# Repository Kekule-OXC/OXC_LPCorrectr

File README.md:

# OXC_LPCorrectr
LPC rebuild baord for the OG XBOX 1.6 motherboard 

-------------------------------------------------------
This documentation describes Open Hardware and is licensed under the CERN OHL v.1.2.

You may redistribute and modify this documentation under the terms of the CERN OHL v.1.2.(http://ohwr.org/cernohl). 
This documentation is distributed WITHOUT ANY EXPRESS OR IMPLIED WARRANTY, INCLUDING OF MERCHANTABILITY, SATISFACTORY QUALITY AND FITNESS FOR A PARTICULAR PURPOSE. 
Please see the CERN OHL v.1.2 for applicable conditions

-------------------------------------------------------

OXC_LPCorrectr   - README.TXT

Files Included in OXC_LPCorrectr.zip (all files must be included when redistributed):

README.TXT
-This file.
	
CHANGES.TXT
-Describes changes made by the original author or anyone else who alters these files.

OXCLPC_V4_gerbers.zip  
-manufactring files for the LPC correctr board v4
- added LFrame wire to ease OpenXenium install, changed d0 jumper pad

OXCLPC_gerbers.zip
-manufacturing files for the LPC correctr board v3

LPC_install.pdf
-install diagram for v3

LPC v4 install.pdf
-install diagram for v4

cern_ohl_v_1_2.pdf
-CERN OHL v.1.2 License.
	
cern_ohl_v_1_2_howto.pdf
-How to use and comply with the CERN OHL v.1.2 License.
	
-------------------------------------------------------

FABRICATION NOTES

PCB
-The PCB is a 0.8mm thick two layer board, with castellated holes on all sides.

-------------------------------------------------------

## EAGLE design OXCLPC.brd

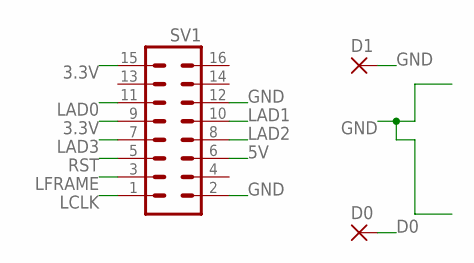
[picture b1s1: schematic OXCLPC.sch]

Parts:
D0, D1: SMD2; SMD1,27-2,54
SV1: MA08-2

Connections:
3.3V: SV1.9, SV1.15
5V: SV1.6
D0: D0.1
GND: D1.1, SV1.2, SV1.12
LAD0: SV1.11
LAD1: SV1.10
LAD2: SV1.8
LAD3: SV1.7
LCLK: SV1.1
LFRAME: SV1.3
RST: SV1.5

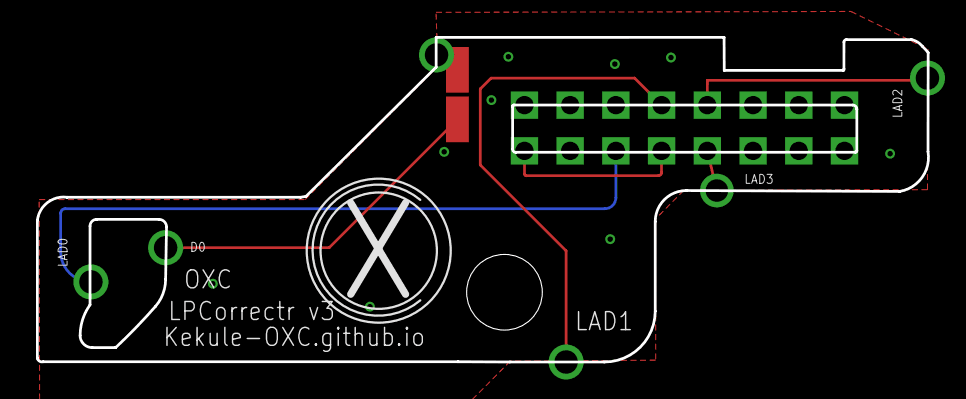
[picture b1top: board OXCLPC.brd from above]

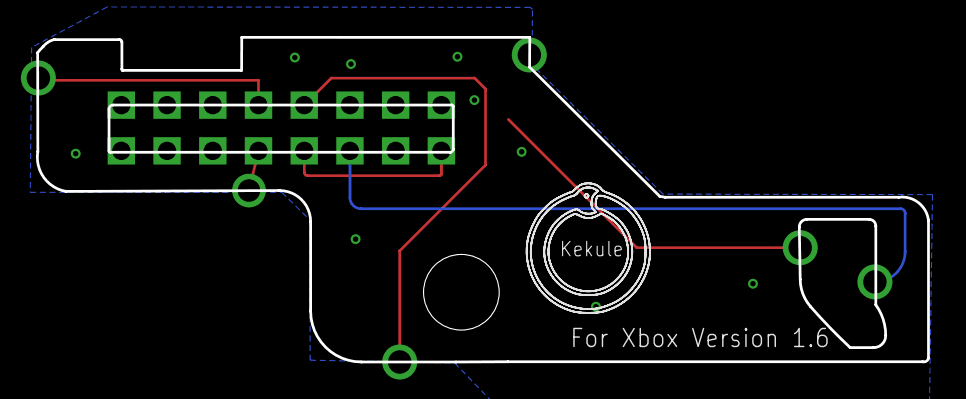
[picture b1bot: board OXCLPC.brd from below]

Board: 2 copper layers, 49.5 x 18.0 mm, 5 parts (2 on the bottom side), 2 nets.

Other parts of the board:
U$1: TEST
U$3: OXC_NO_TM

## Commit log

2019-03-20 Add files via upload
    uploaded gerbers
2019-04-16 updated and added gerbers
2019-04-16 changed logo
2019-04-16 changed GND hole to appease the pcb manufacturers
2019-04-16 fixed logo
2019-04-29 add install instructions
2019-04-29 add install pdf
2019-08-22 Add files via upload
    updated LPC install pdf
2020-06-15 added v4 gerbers
    v4 includes a line to connect LFrame for OpenXenium and other mod chips.
2020-06-15 install diagram for v4
2020-06-28 fixed the gerbers for v4
